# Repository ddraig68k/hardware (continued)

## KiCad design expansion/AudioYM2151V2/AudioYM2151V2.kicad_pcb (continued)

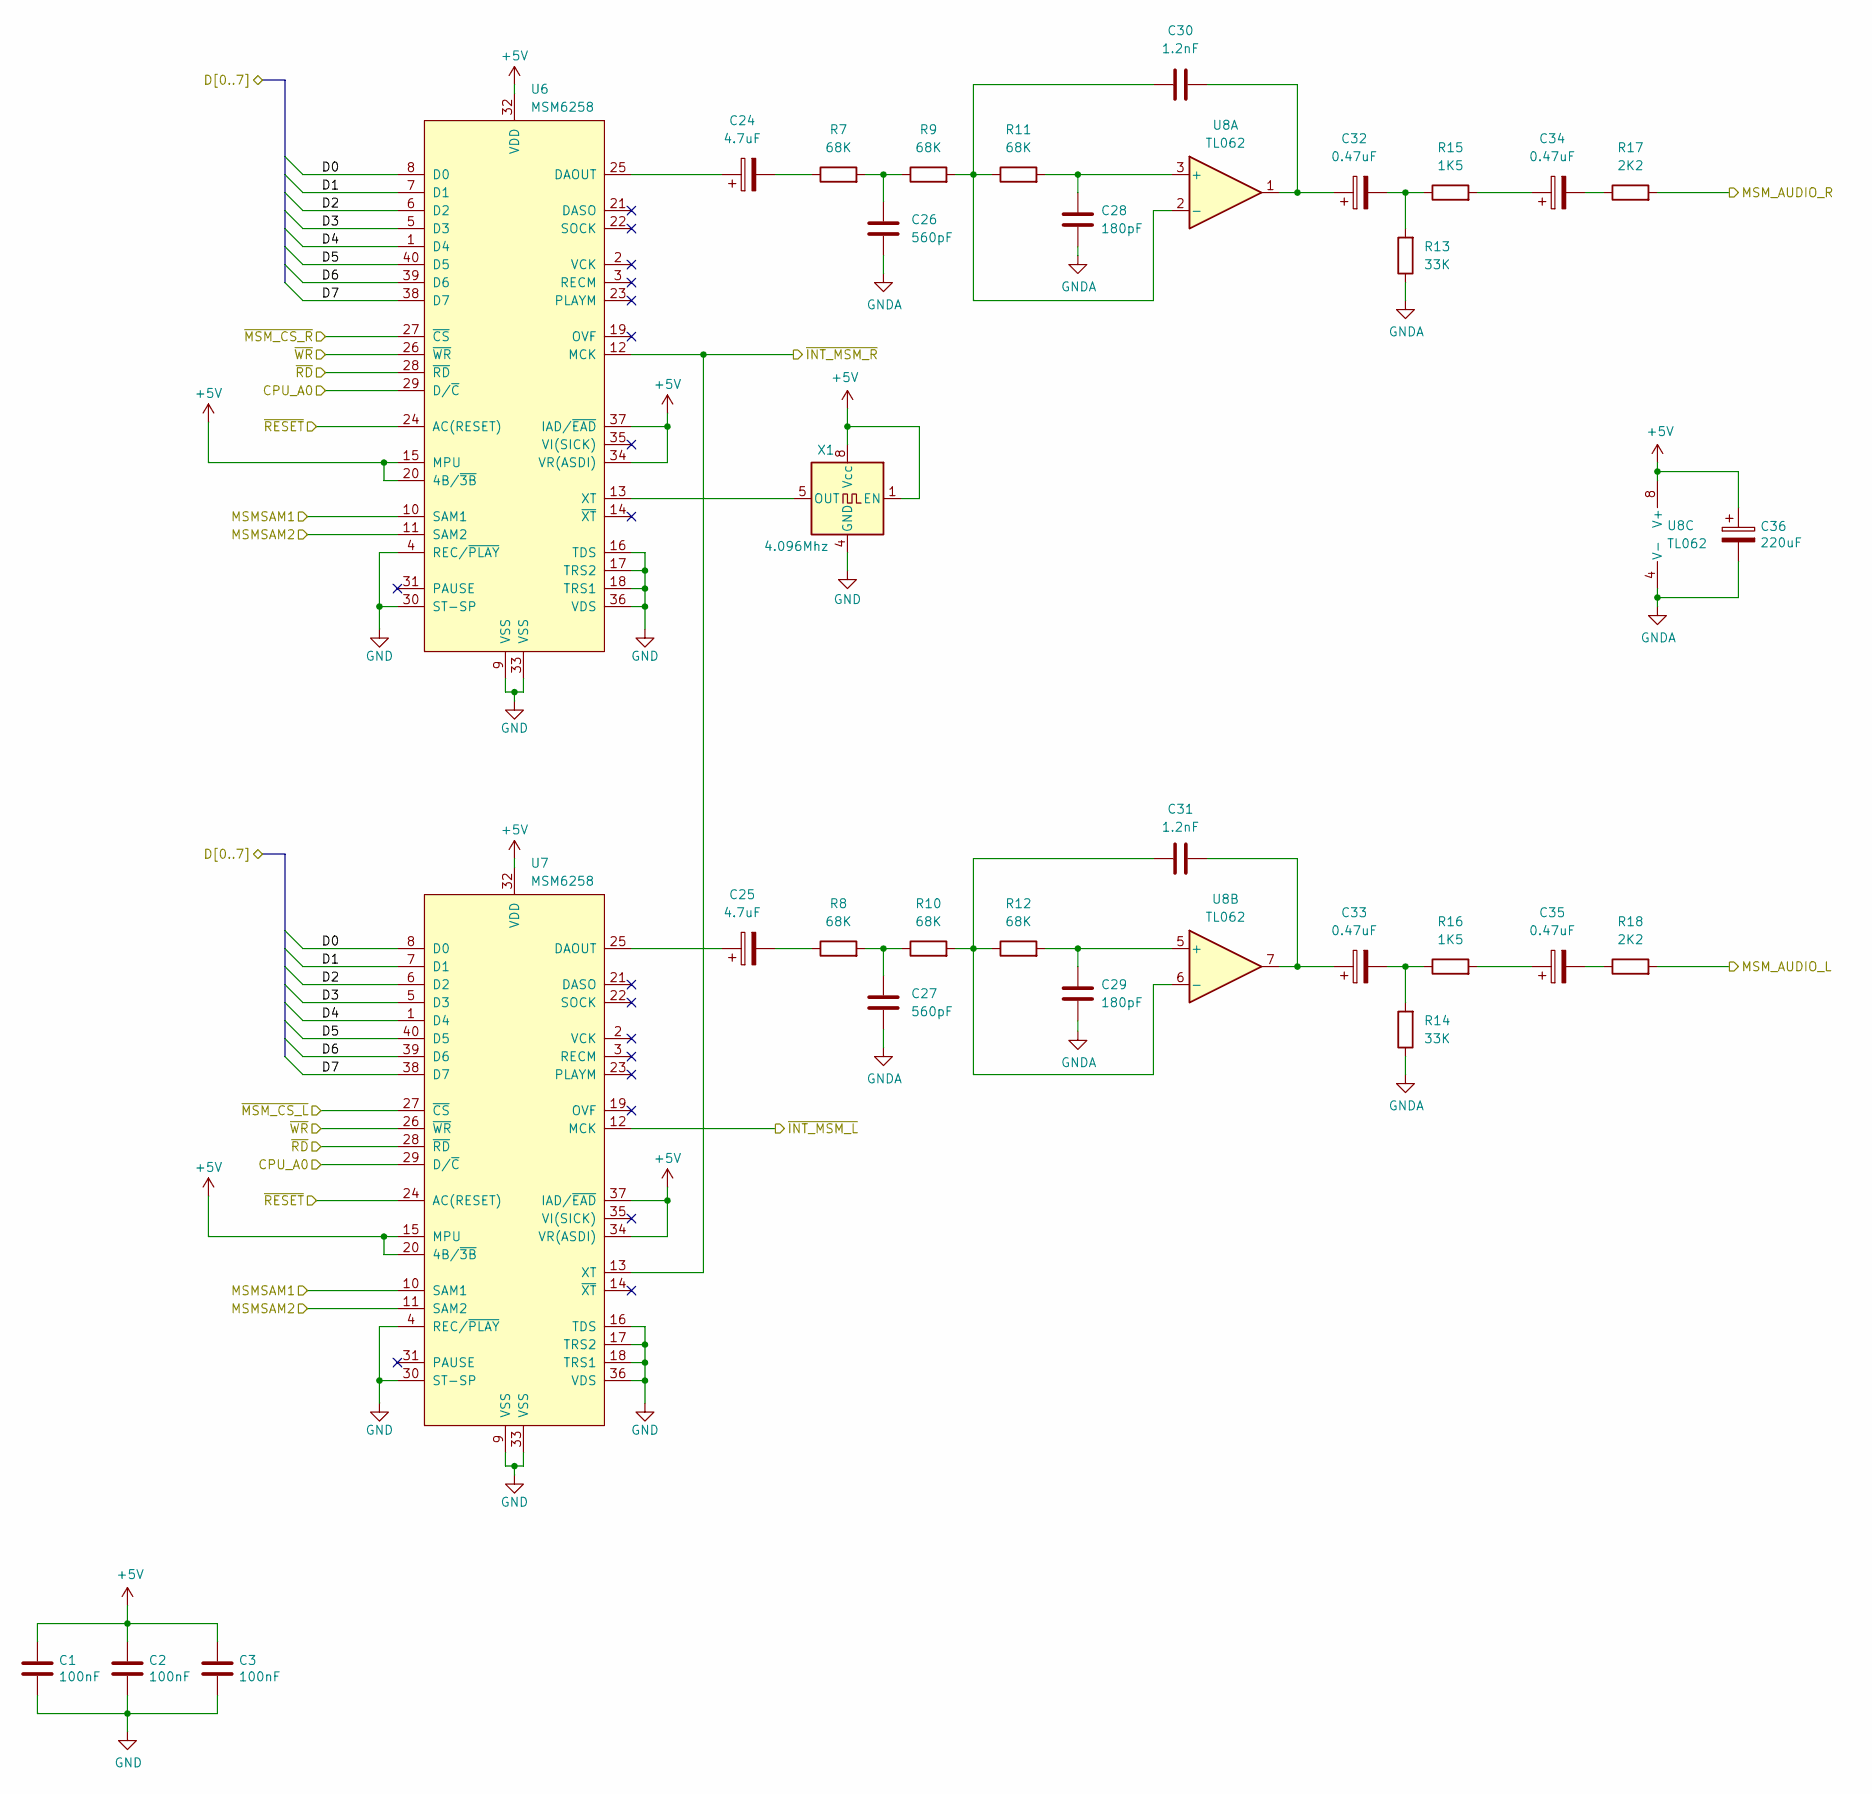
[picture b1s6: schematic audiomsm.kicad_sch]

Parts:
C1, C2, C3: 100nF; C_Disc_D5.0mm_W2.5mm_P2.50mm
C24, C25: 4.7uF; CP_Radial_D5.0mm_P2.50mm
C26, C27: 560pF; C_Disc_D5.0mm_W2.5mm_P2.50mm
C28, C29: 180pF; C_Disc_D5.0mm_W2.5mm_P2.50mm
C30, C31: 1.2nF; C_Disc_D5.0mm_W2.5mm_P2.50mm
C32, C33, C34, C35: 0.47uF; CP_Radial_D5.0mm_P2.50mm
C36: 220uF; CP_Radial_D5.0mm_P2.50mm
R7, R8, R9, R10, R11, R12: 68K; R_Axial_DIN0207_L6.3mm_D2.5mm_P10.16mm_Horizontal
R13, R14: 33K; R_Axial_DIN0207_L6.3mm_D2.5mm_P10.16mm_Horizontal
R15, R16: 1K5; R_Axial_DIN0207_L6.3mm_D2.5mm_P10.16mm_Horizontal
R17, R18: 2K2; R_Axial_DIN0207_L6.3mm_D2.5mm_P10.16mm_Horizontal
U6, U7: MSM6258; DIP-40_W15.24mm_Socket
U8: TL062; DIP-8_W7.62mm_Socket
X1: 4.096Mhz; Oscillator_DIP-8

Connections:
/Audio/Amplifier/MSM_AUDIO_L: R18.2; also elsewhere on the board
/Audio/Amplifier/MSM_AUDIO_R: R17.2; also elsewhere on the board
/Audio/CPU/CPU_A0: U6.29 (D/~C), U7.29 (D/~C); also elsewhere on the board
/Audio/CPU/MSMSAM1: U6.10 (SAM1), U7.10 (SAM1); also elsewhere on the board
/Audio/CPU/MSMSAM2: U6.11 (SAM2), U7.11 (SAM2); also elsewhere on the board
/Audio/CPU/~INT_MSM_L: U7.12 (MCK); also elsewhere on the board
/Audio/CPU/~INT_MSM_R: U6.12 (MCK), U7.13 (XT); also elsewhere on the board
/Audio/CPU/~RD: U6.28 (~RD), U7.28 (~RD); also elsewhere on the board
/Audio/CPU/~WR: U6.26 (~WR), U7.26 (~WR); also elsewhere on the board
/Audio/MSM Audio/~MSM_CS_L: U7.27 (~CS); also elsewhere on the board
/Audio/MSM Audio/~MSM_CS_R: U6.27 (~CS); also elsewhere on the board
/D0: U6.8 (D0), U7.8 (D0); also elsewhere on the board
/D1: U6.7 (D1), U7.7 (D1); also elsewhere on the board
/D2: U6.6 (D2), U7.6 (D2); also elsewhere on the board
/D3: U6.5 (D3), U7.5 (D3); also elsewhere on the board
/D4: U6.1 (D4), U7.1 (D4); also elsewhere on the board
/D5: U6.40 (D5), U7.40 (D5); also elsewhere on the board
/D6: U6.39 (D6), U7.39 (D6); also elsewhere on the board
/D7: U6.38 (D7), U7.38 (D7); also elsewhere on the board
/~RESET: U6.24 (AC(RESET)), U7.24 (AC(RESET)); also elsewhere on the board
GND: C1.2, C2.2, C3.2, U6.4 (REC/~PLAY), U6.9 (VSS), U6.16 (TDS), U6.17 (TRS2), U6.18 (TRS1), U6.30 (ST-SP), U6.33 (VSS), U6.36 (VDS), U7.4 (REC/~PLAY), U7.9 (VSS), U7.16 (TDS), U7.17 (TRS2), U7.18 (TRS1), U7.30 (ST-SP), U7.33 (VSS), U7.36 (VDS), X1.4 (GND); also elsewhere on the board
GNDA: C26.2, C27.2, C28.2, C29.2, C36.2, R13.1, R14.1, U8.4 (V-); also elsewhere on the board
unnamed: C24.2, R7.1
unnamed: C25.2, R8.1
unnamed: C26.1, R7.2, R9.1
unnamed: C27.1, R8.2, R10.1
unnamed: C30.1, C32.1, U8.1
unnamed: C31.2, C33.1, U8.7
unnamed: C32.2, R13.2, R15.1
unnamed: C33.2, R14.2, R16.1
unnamed: C34.1, R15.2
unnamed: C34.2, R17.1
unnamed: C35.1, R16.2
unnamed: C35.2, R18.1
unnamed: C24.1, U6.25 (DAOUT)
unnamed: U6.13 (XT), X1.5 (OUT)
unnamed: C25.1, U7.25 (DAOUT)
unnamed: C28.1, R11.2, U8.3 (+)
unnamed: C30.2, R9.2, R11.1, U8.2 (-)
unnamed: C29.1, R12.2, U8.5 (+)
unnamed: C31.1, R10.2, R12.1, U8.6 (-)

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
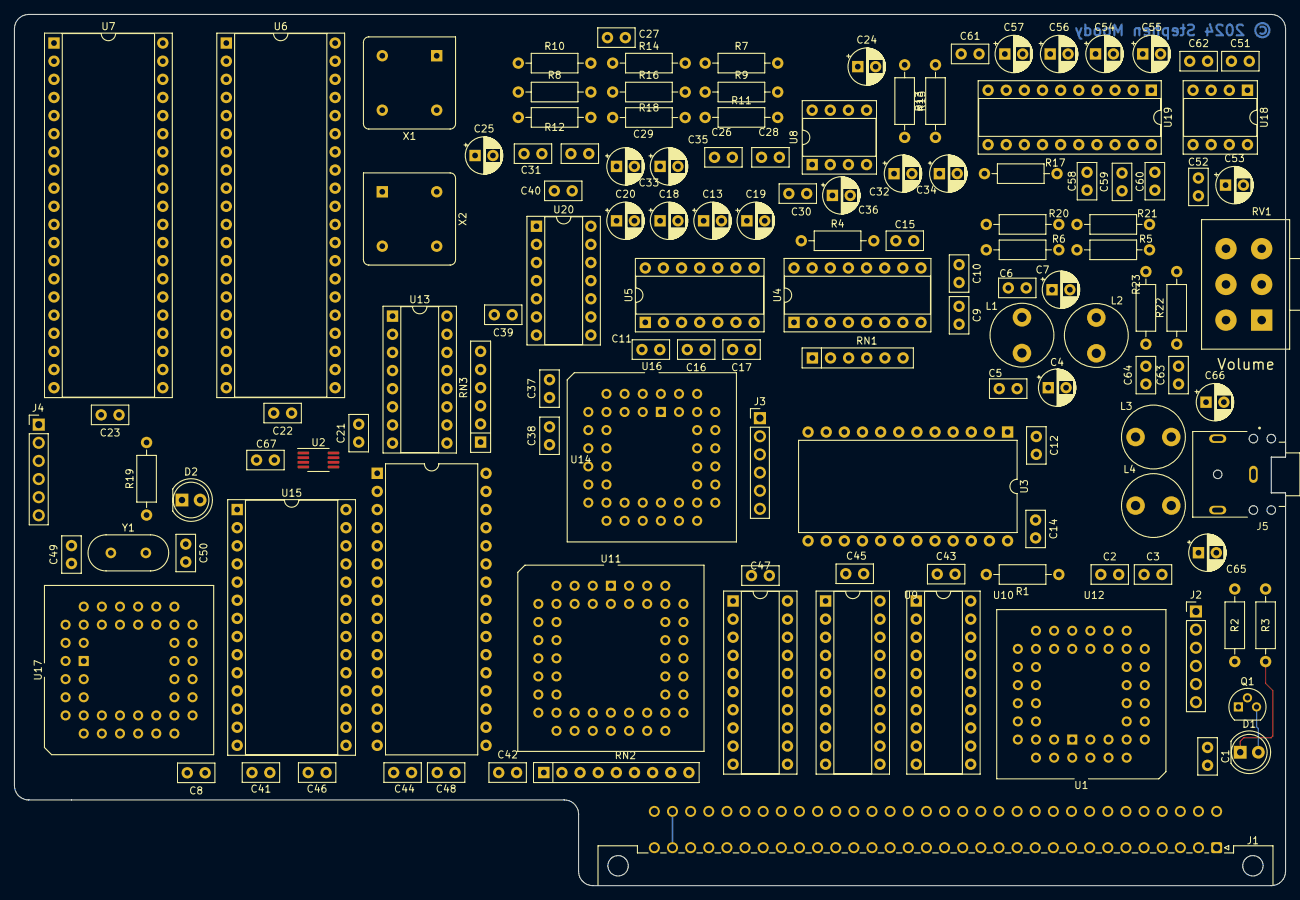
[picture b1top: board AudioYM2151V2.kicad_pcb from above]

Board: 4 copper layers, 178.0 x 122.0 mm, 129 parts (0 on the bottom side), 182 nets.

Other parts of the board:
C21, C22, C23, C37, C38, C39, C40, C41, C42, C43, C44, C45, C46, C47, C48, C67: 100nF; C_Disc_D5.0mm_W2.5mm_P2.50mm
D2: LED; LED_D5.0mm
R19: 220R; R_Axial_DIN0207_L6.3mm_D2.5mm_P10.16mm_Horizontal

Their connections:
GND: C21.2, C22.2, C23.2, C37.2, C38.2, C39.2, C40.2, C41.2, C42.2, C43.2, C44.2, C45.2, C46.2, C47.2, C48.2, C67.2; also elsewhere on the board
unnamed: D2.1 (K), R19.1

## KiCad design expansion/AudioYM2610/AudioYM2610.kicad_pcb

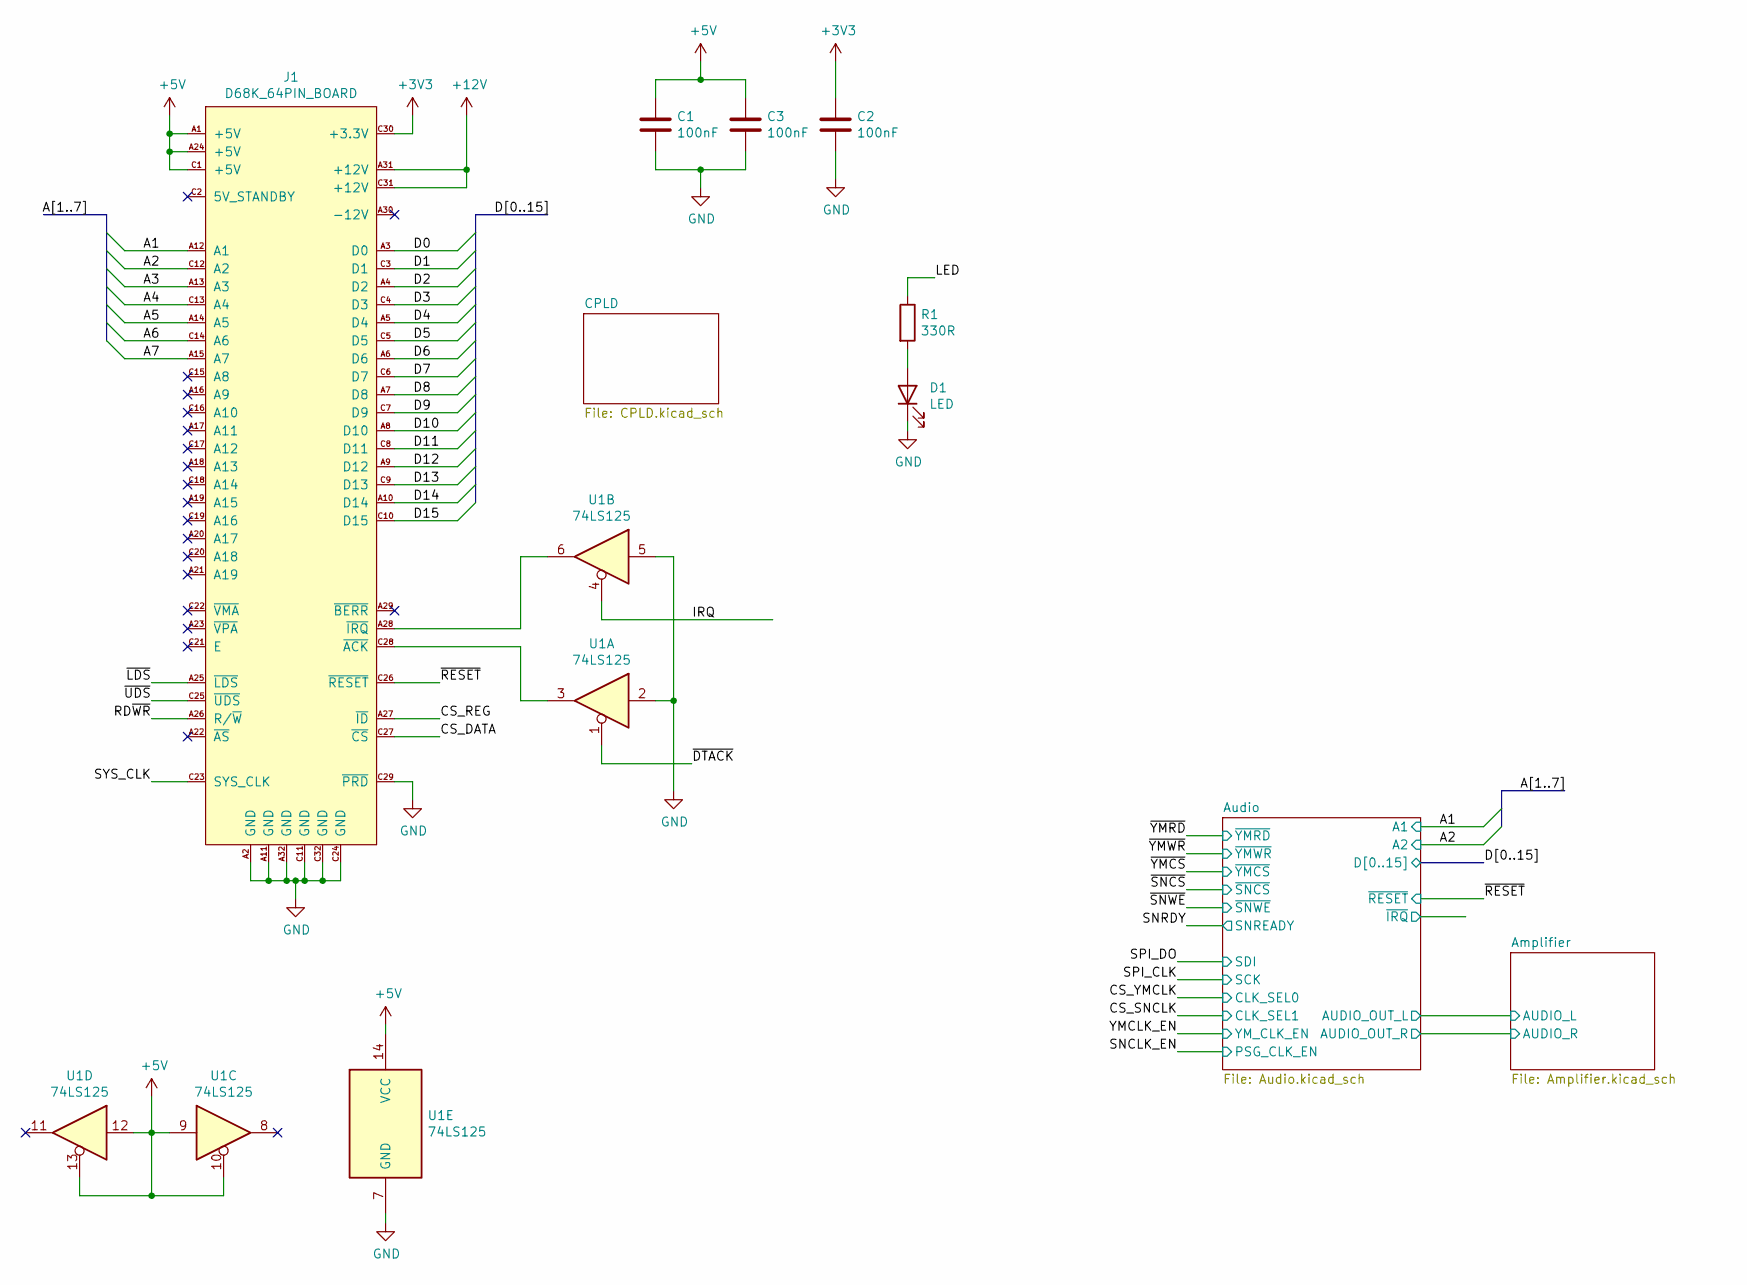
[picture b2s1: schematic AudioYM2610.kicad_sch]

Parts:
C1, C2, C3: 100nF; C_Disc_D5.0mm_W2.5mm_P2.50mm
D1: LED; LED_D5.0mm_Clear
J1: D68K_64PIN_BOARD; DIN41612_C_2x32_Male_Horizontal_THT
R1: 330R; R_Axial_DIN0207_L6.3mm_D2.5mm_P10.16mm_Horizontal
U1: 74LS125; DIP-14_W7.62mm_Socket

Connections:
+3V3: C2.1, J1.C30 (+3.3V); also elsewhere on the board
+5V: C1.1, C3.1, J1.A1 (+5V), J1.A24 (+5V), J1.C1 (+5V), U1.9, U1.10, U1.12, U1.13, U1.14 (VCC); also elsewhere on the board
+12V: J1.A31 (+12V), J1.C31 (+12V); also elsewhere on the board
/A1: J1.A12 (A1); also elsewhere on the board
/A2: J1.C12 (A2); also elsewhere on the board
/A3: J1.A13 (A3); also elsewhere on the board
/A4: J1.C13 (A4); also elsewhere on the board
/A5: J1.A14 (A5); also elsewhere on the board
/A6: J1.C14 (A6); also elsewhere on the board
/A7: J1.A15 (A7); also elsewhere on the board
/CS_DATA: J1.C27 (~CS); also elsewhere on the board
/CS_REG: J1.A27 (~ID); also elsewhere on the board
/D0: J1.A3 (D0); also elsewhere on the board
/D1: J1.C3 (D1); also elsewhere on the board
/D2: J1.A4 (D2); also elsewhere on the board
/D3: J1.C4 (D3); also elsewhere on the board
/D4: J1.A5 (D4); also elsewhere on the board
/D5: J1.C5 (D5); also elsewhere on the board
/D6: J1.A6 (D6); also elsewhere on the board
/D7: J1.C6 (D7); also elsewhere on the board
/D8: J1.A7 (D8); also elsewhere on the board
/D9: J1.C7 (D9); also elsewhere on the board
/D10: J1.A8 (D10); also elsewhere on the board
/D11: J1.C8 (D11); also elsewhere on the board
/D12: J1.A9 (D12); also elsewhere on the board
/D13: J1.C9 (D13); also elsewhere on the board
/D14: J1.A10 (D14); also elsewhere on the board
/D15: J1.C10 (D15); also elsewhere on the board
/IRQ: U1.4; also elsewhere on the board
/LED: R1.1; also elsewhere on the board
/RD~WR: J1.A26 (R/~W); also elsewhere on the board
/SYS_CLK: J1.C23 (SYS_CLK); also elsewhere on the board
/~DTACK: U1.1; also elsewhere on the board
/~LDS: J1.A25 (~LDS); also elsewhere on the board
/~RESET: J1.C26 (~RESET); also elsewhere on the board
/~UDS: J1.C25 (~UDS); also elsewhere on the board
GND: C1.2, C2.2, C3.2, D1.1 (K), J1.A2 (GND), J1.A11 (GND), J1.A32 (GND), J1.C11 (GND), J1.C24 (GND), J1.C29 (~PRD), J1.C32 (GND), U1.2, U1.5, U1.7 (GND); also elsewhere on the board
unnamed: D1.2 (A), R1.2
unnamed: J1.A28 (~IRQ), U1.6
unnamed: J1.C28 (~ACK), U1.3

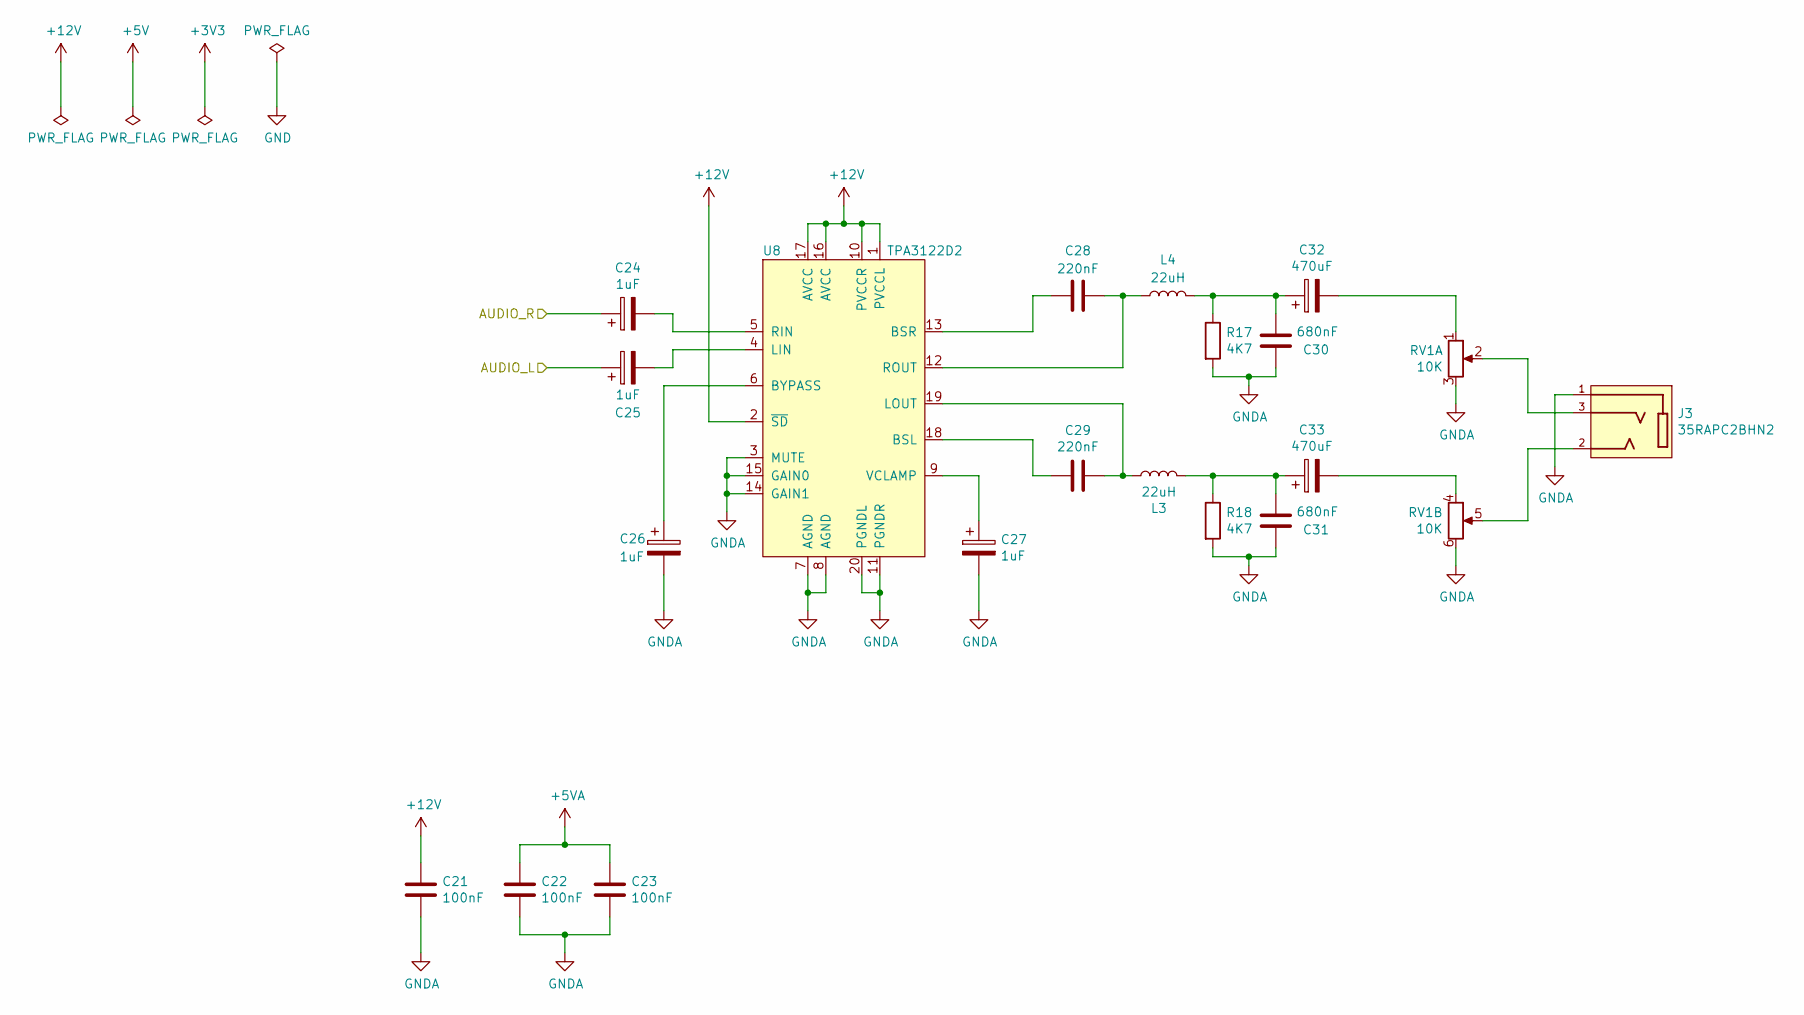
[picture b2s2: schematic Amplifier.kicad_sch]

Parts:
C21, C22, C23: 100nF; C_Disc_D5.0mm_W2.5mm_P2.50mm
C24, C25, C26, C27: 1uF; CP_Radial_D5.0mm_P2.50mm
C28, C29: 220nF; C_Disc_D5.0mm_W2.5mm_P2.50mm
C30, C31: 680nF; C_Disc_D5.0mm_W2.5mm_P2.50mm
C32, C33: 470uF; CP_Radial_D8.0mm_P5.00mm
J3: 35RAPC2BHN2; SWITCHCRAFT_35RAPC2BHN2; PARTREV L
L3, L4: 22uH; L_Radial_D8.7mm_P5.00mm_Fastron_07HCP
R17, R18: 4K7; R_Axial_DIN0207_L6.3mm_D2.5mm_P10.16mm_Horizontal
RV1: 10K; Potentiometer_Alps_RK163_Dual_Horizontal
U8: TPA3122D2; DIP-20_W7.62mm_Socket

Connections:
+5VA: C22.1, C23.1; also elsewhere on the board
+12V: C21.1, U8.1 (PVCCL), U8.2 (~SD), U8.10 (PVCCR), U8.16 (AVCC), U8.17 (AVCC); also elsewhere on the board
/Amplifier/AUDIO_L: C25.1; also elsewhere on the board
/Audio/AUDIO_OUT_R: C24.1; also elsewhere on the board
GNDA: C21.2, C22.2, C23.2, C26.2, C27.2, C30.1, C31.1, J3.1, R17.2, R18.2, RV1.3, RV1.6, U8.3 (MUTE), U8.7 (AGND), U8.8 (AGND), U8.11 (PGNDR), U8.14 (GAIN1), U8.15 (GAIN0), U8.20 (PGNDL); also elsewhere on the board
unnamed: C24.2, U8.5 (RIN)
unnamed: C25.2, U8.4 (LIN)
unnamed: C26.1, U8.6 (BYPASS)
unnamed: C27.1, U8.9 (VCLAMP)
unnamed: C28.1, U8.13 (BSR)
unnamed: C28.2, L4.1, U8.12 (ROUT)
unnamed: C29.1, L3.1, U8.19 (LOUT)
unnamed: C29.2, U8.18 (BSL)
unnamed: C30.2, C32.1, L4.2, R17.1
unnamed: C31.2, C33.1, L3.2, R18.1
unnamed: C32.2, RV1.1
unnamed: C33.2, RV1.4
unnamed: J3.2, RV1.5
unnamed: J3.3, RV1.2

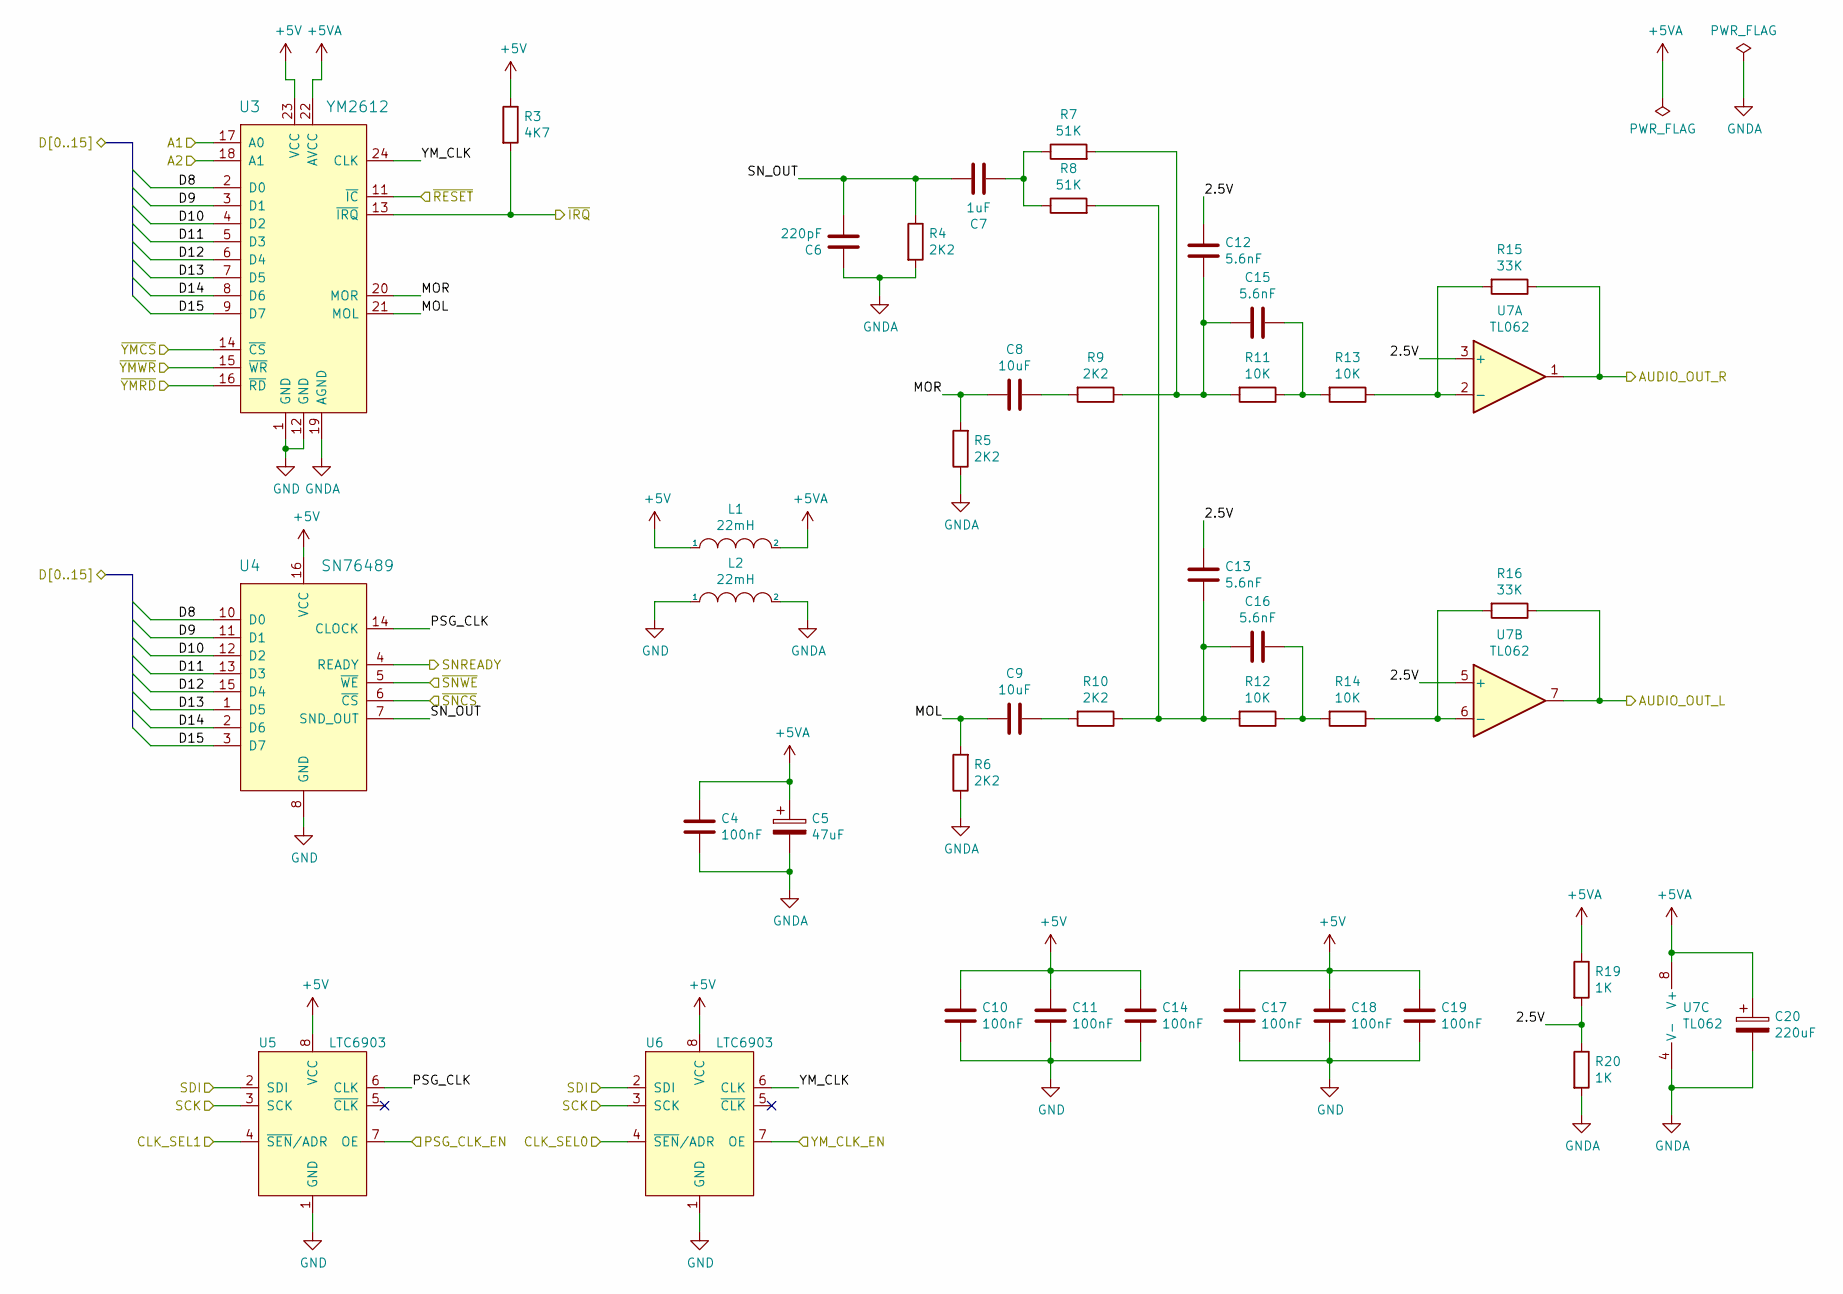
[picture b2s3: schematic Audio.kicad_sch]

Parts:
C4, C10, C11, C14, C17, C18, C19: 100nF; C_Disc_D5.0mm_W2.5mm_P2.50mm
C5: 47uF; CP_Radial_D5.0mm_P2.50mm
C6: 220pF; C_Disc_D5.0mm_W2.5mm_P2.50mm
C7: 1uF; C_Disc_D5.0mm_W2.5mm_P2.50mm
C8, C9: 10uF; C_Disc_D5.0mm_W2.5mm_P2.50mm
C12, C13, C15, C16: 5.6nF; C_Disc_D5.0mm_W2.5mm_P2.50mm
C20: 220uF; CP_Radial_D5.0mm_P2.50mm
L1, L2: 22mH; L_Radial_D8.7mm_P5.00mm_Fastron_07HCP
R3: 4K7; R_Axial_DIN0207_L6.3mm_D2.5mm_P10.16mm_Horizontal
R4, R5, R6, R9, R10: 2K2; R_Axial_DIN0207_L6.3mm_D2.5mm_P10.16mm_Horizontal
R7, R8: 51K; R_Axial_DIN0207_L6.3mm_D2.5mm_P10.16mm_Horizontal
R11, R12, R13, R14: 10K; R_Axial_DIN0207_L6.3mm_D2.5mm_P10.16mm_Horizontal
R15, R16: 33K; R_Axial_DIN0207_L6.3mm_D2.5mm_P10.16mm_Horizontal
R19, R20: 1K; R_Axial_DIN0207_L6.3mm_D2.5mm_P10.16mm_Horizontal
U3: YM2612; DIP-24_W15.24mm_Socket
U4: SN76489; DIP-16_W7.62mm_Socket
U5, U6: LTC6903; SOP65P490X110-8N
U7: TL062; DIP-8_W7.62mm_Socket

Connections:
+5V: C10.1, C11.1, C14.1, C17.1, C18.1, C19.1, L1.1, R3.1, U3.23 (VCC), U4.16 (VCC), U5.8 (VCC), U6.8 (VCC); also elsewhere on the board
+5VA: C4.1, C5.1, C20.1, L1.2, R19.1, U3.22 (AVCC), U7.8 (V+); also elsewhere on the board
/A1: U3.17 (A0); also elsewhere on the board
/A2: U3.18 (A1); also elsewhere on the board
/Amplifier/AUDIO_L: R16.1, U7.7; also elsewhere on the board
/Audio/2.5V: C12.1, C13.1, R19.2, R20.1, U7.3 (+), U7.5 (+)
/Audio/AUDIO_OUT_R: R15.1, U7.1; also elsewhere on the board
/Audio/MOL: C9.2, R6.2, U3.21 (MOL)
/Audio/MOR: C8.2, R5.2, U3.20 (MOR)
/Audio/PSG_CLK: U4.14 (CLOCK), U5.6 (CLK)
/Audio/SN_OUT: C6.2, C7.1, R4.1, U4.7 (SND_OUT)
/Audio/YM_CLK: U3.24 (CLK), U6.6 (CLK)
/CS_SNCLK: U5.4 (~SEN/ADR); also elsewhere on the board
/CS_YMCLK: U6.4 (~SEN/ADR); also elsewhere on the board
/D8: U3.2 (D0), U4.10 (D0); also elsewhere on the board
/D9: U3.3 (D1), U4.11 (D1); also elsewhere on the board
/D10: U3.4 (D2), U4.12 (D2); also elsewhere on the board
/D11: U3.5 (D3), U4.13 (D3); also elsewhere on the board
/D12: U3.6 (D4), U4.15 (D4); also elsewhere on the board
/D13: U3.7 (D5), U4.1 (D5); also elsewhere on the board
/D14: U3.8 (D6), U4.2 (D6); also elsewhere on the board
/D15: U3.9 (D7), U4.3 (D7); also elsewhere on the board
/IRQ: R3.2, U3.13 (~IRQ); also elsewhere on the board
/SNCLK_EN: U5.7 (OE); also elsewhere on the board
/SNRDY: U4.4 (READY); also elsewhere on the board
/SPI_CLK: U5.3 (SCK), U6.3 (SCK); also elsewhere on the board
/SPI_DO: U5.2 (SDI), U6.2 (SDI); also elsewhere on the board
/YMCLK_EN: U6.7 (OE); also elsewhere on the board
/~RESET: U3.11 (~IC); also elsewhere on the board
/~SNCS: U4.6 (~CS); also elsewhere on the board
/~SNWE: U4.5 (~WE); also elsewhere on the board
/~YMCS: U3.14 (~CS); also elsewhere on the board
/~YMRD: U3.16 (~RD); also elsewhere on the board
/~YMWR: U3.15 (~WR); also elsewhere on the board
GND: C10.2, C11.2, C14.2, C17.2, C18.2, C19.2, L2.1, U3.1 (GND), U3.12 (GND), U4.8 (GND), U5.1 (GND), U6.1 (GND); also elsewhere on the board
GNDA: C4.2, C5.2, C6.1, C20.2, L2.2, R4.2, R5.1, R6.1, R20.2, U3.19 (AGND), U7.4 (V-); also elsewhere on the board
unnamed: C7.2, R7.1, R8.1
unnamed: C8.1, R9.2
unnamed: C9.1, R10.2
unnamed: C12.2, C15.2, R7.2, R9.1, R11.2
unnamed: C13.2, C16.2, R8.2, R10.1, R12.2
unnamed: C15.1, R11.1, R13.2
unnamed: C16.1, R12.1, R14.2
unnamed: R13.1, R15.2, U7.2 (-)
unnamed: R14.1, R16.2, U7.6 (-)

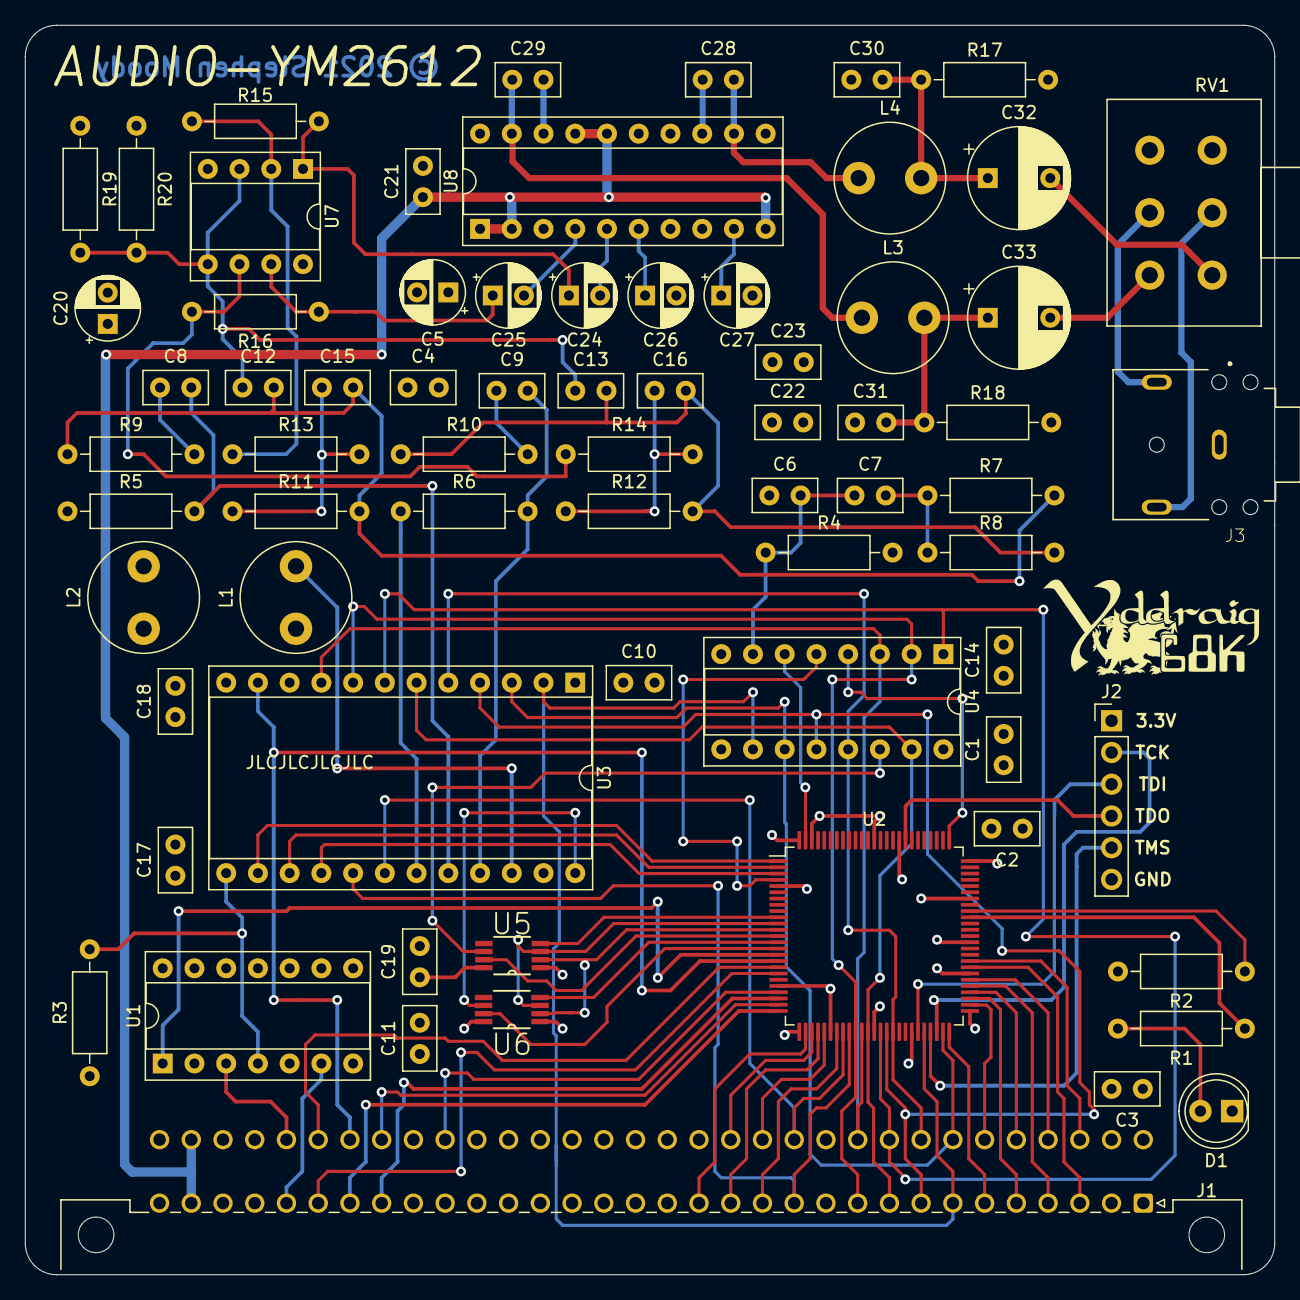
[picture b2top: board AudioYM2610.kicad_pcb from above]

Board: 4 copper layers, 100.0 x 100.0 mm, 70 parts (0 on the bottom side), 90 nets.

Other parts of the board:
J2: JTAG; PinHeader_1x06_P2.54mm_Vertical
R2: 10K; R_Axial_DIN0207_L6.3mm_D2.5mm_P10.16mm_Horizontal
U2: XC95144XL-TQ100; TQFP-100_14x14mm_P0.5mm

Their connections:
+3V3: J2.1, U2.5, U2.26, U2.38, U2.51, U2.57, U2.88, U2.98; also elsewhere on the board
/A1: U2.34; also elsewhere on the board
/A2: U2.33; also elsewhere on the board
/A3: U2.32; also elsewhere on the board
/A4: U2.30; also elsewhere on the board
/A5: U2.29; also elsewhere on the board
/A6: U2.28; also elsewhere on the board
/A7: U2.27; also elsewhere on the board
/CS_DATA: U2.18; also elsewhere on the board
/CS_REG: U2.19; also elsewhere on the board
/CS_SNCLK: U2.10; also elsewhere on the board
/CS_YMCLK: U2.14; also elsewhere on the board
/D0: U2.58; also elsewhere on the board
/D1: U2.59; also elsewhere on the board
/D2: U2.55; also elsewhere on the board
/D3: U2.56; also elsewhere on the board
/D4: U2.53; also elsewhere on the board
/D5: U2.54; also elsewhere on the board
/D6: U2.50; also elsewhere on the board
/D7: U2.52; also elsewhere on the board
/D8: U2.46; also elsewhere on the board
/D9: U2.49; also elsewhere on the board
/D10: U2.40; also elsewhere on the board
/D11: U2.41; also elsewhere on the board
/D12: U2.37; also elsewhere on the board
/D13: U2.39; also elsewhere on the board
/D14: U2.35; also elsewhere on the board
/D15: U2.36; also elsewhere on the board
/LED: U2.66; also elsewhere on the board
/RD~WR: U2.25; also elsewhere on the board
/SNCLK_EN: U2.13; also elsewhere on the board
/SNRDY: U2.76; also elsewhere on the board
/SPI_CLK: U2.11; also elsewhere on the board
/SPI_DI: R2.1, U2.67
/SPI_DO: U2.12; also elsewhere on the board
/SYS_CLK: U2.22; also elsewhere on the board
/YMCLK_EN: U2.15; also elsewhere on the board
/~DTACK: U2.16; also elsewhere on the board
/~LDS: U2.23; also elsewhere on the board
/~RESET: U2.17; also elsewhere on the board
/~SNCS: U2.99; also elsewhere on the board
/~SNWE: U2.4; also elsewhere on the board
/~UDS: U2.24; also elsewhere on the board
/~YMCS: U2.1; also elsewhere on the board
/~YMRD: U2.3; also elsewhere on the board
/~YMWR: U2.2; also elsewhere on the board
GND: J2.6, R2.2, U2.21, U2.31, U2.44, U2.62, U2.69, U2.75, U2.84, U2.100; also elsewhere on the board
unnamed: J2.2, U2.48
unnamed: J2.3, U2.45
unnamed: J2.4, U2.83
unnamed: J2.5, U2.47
